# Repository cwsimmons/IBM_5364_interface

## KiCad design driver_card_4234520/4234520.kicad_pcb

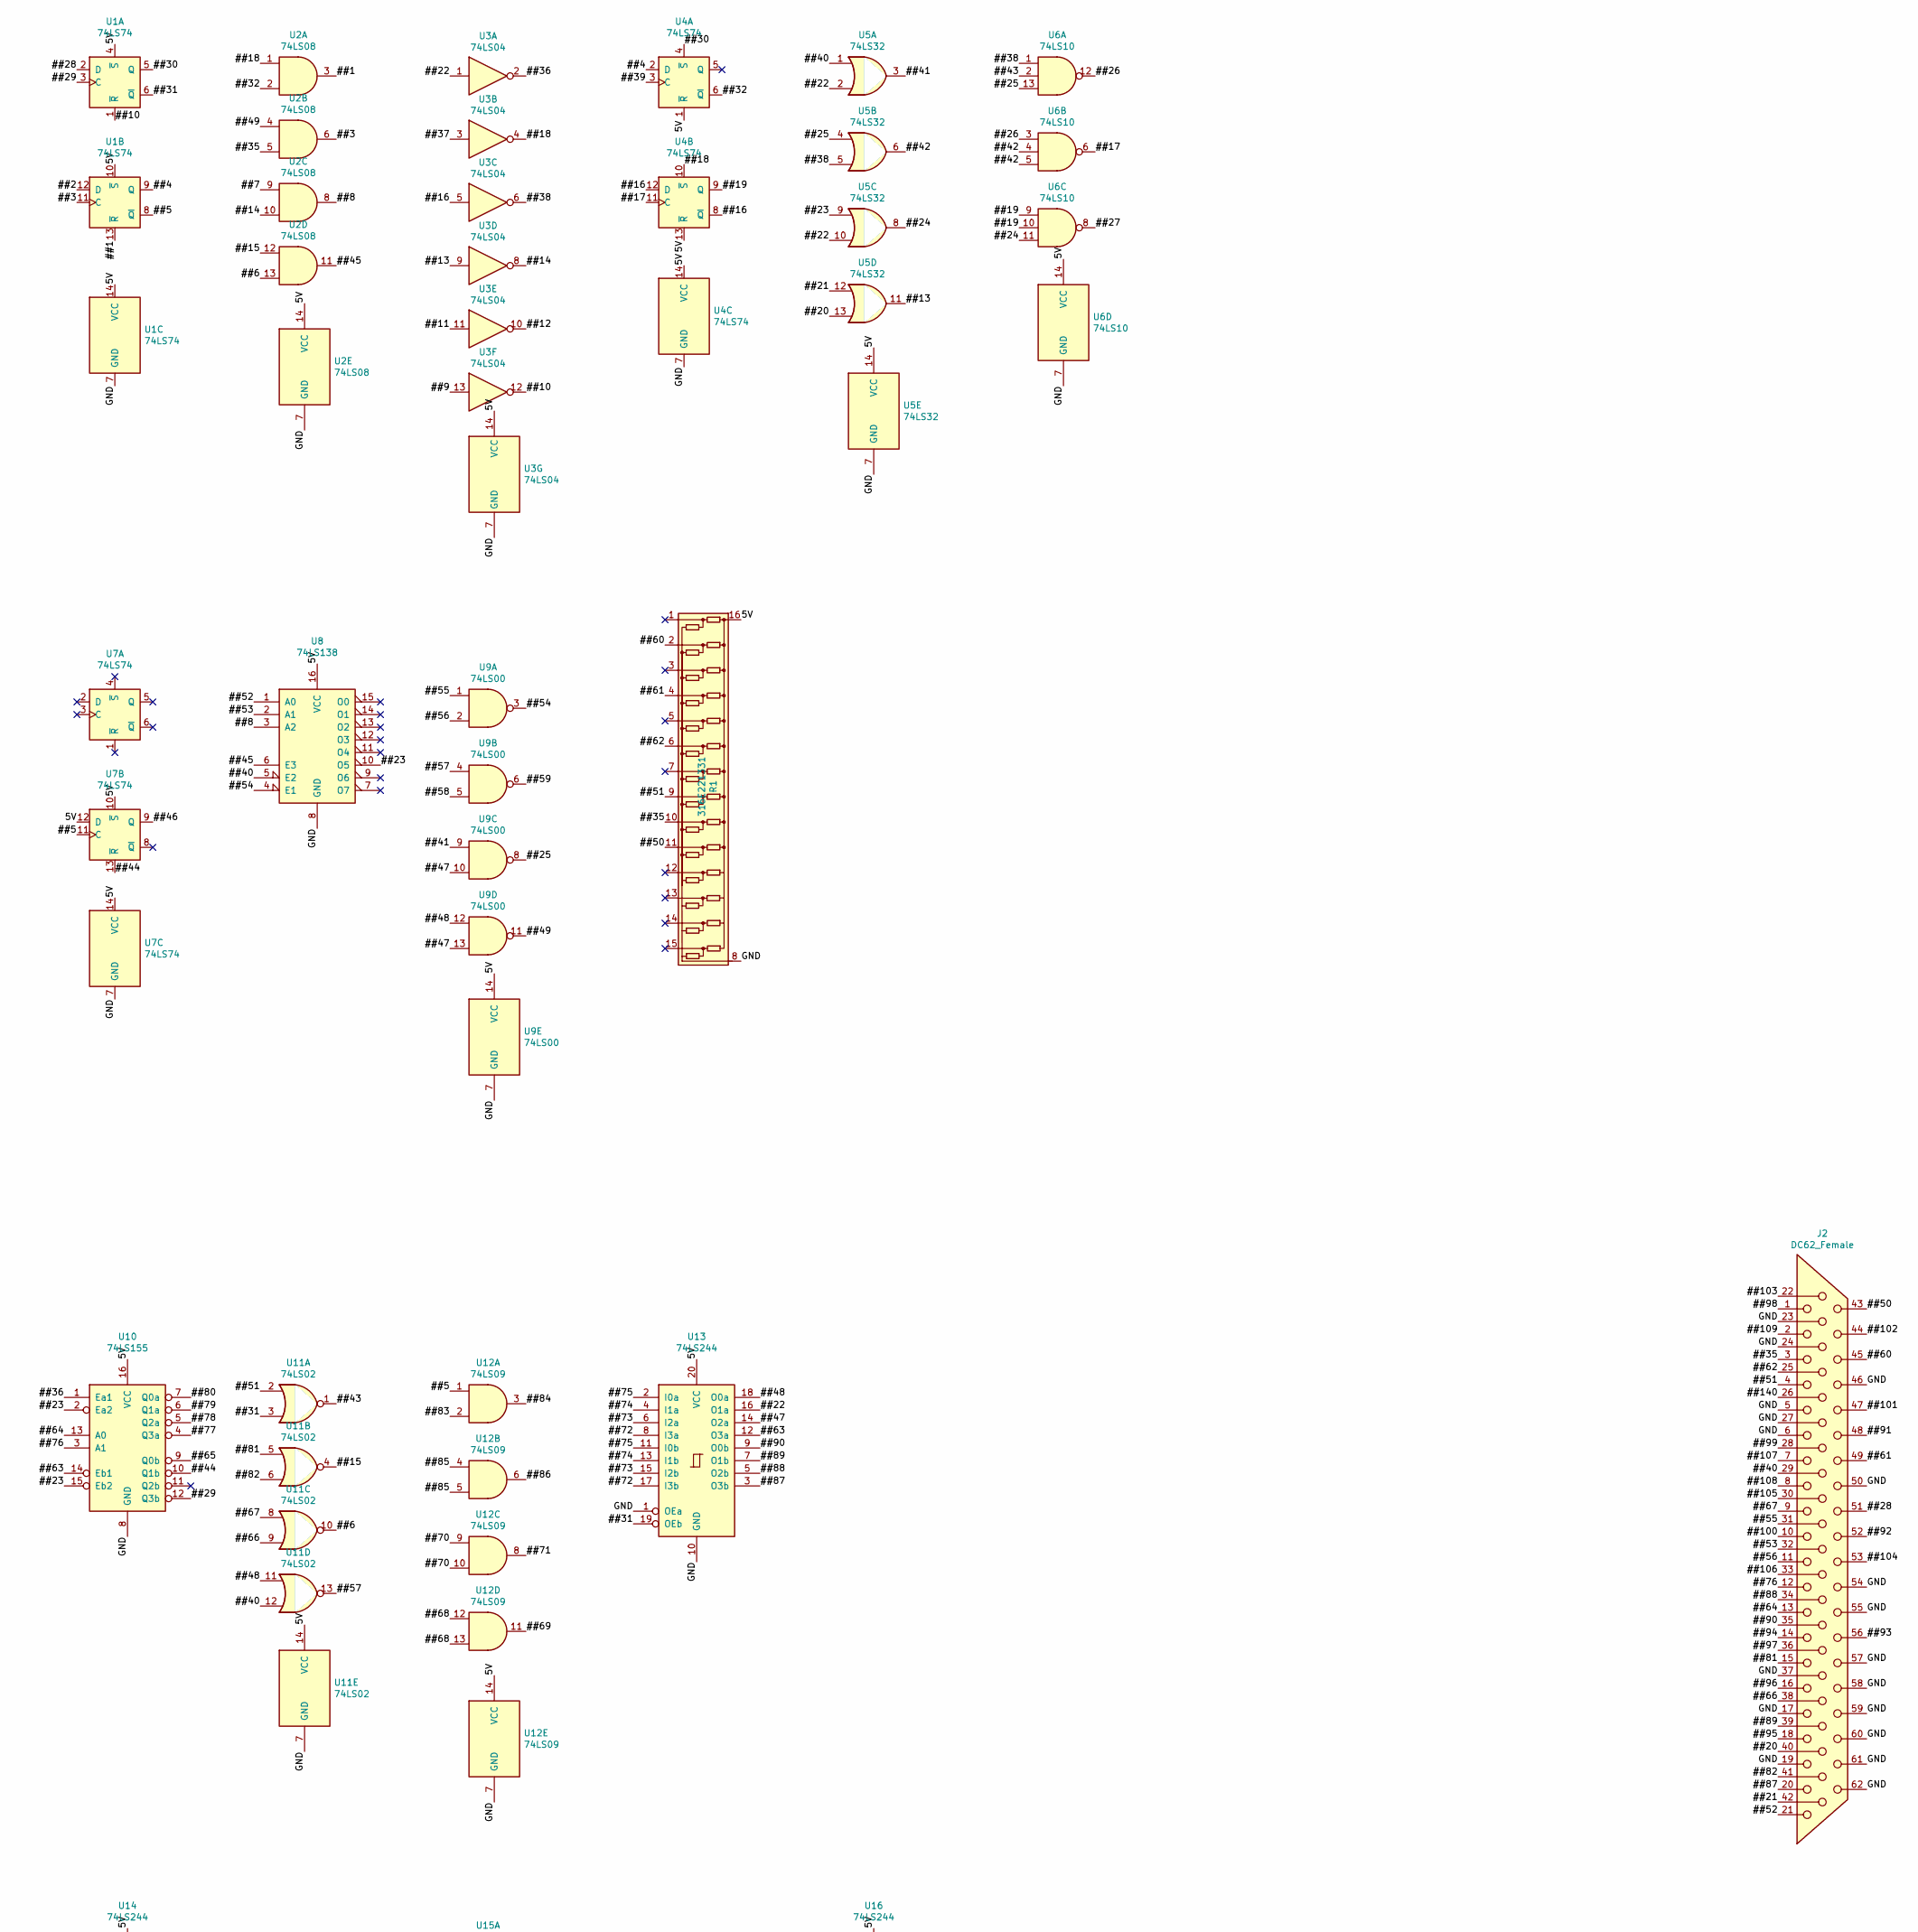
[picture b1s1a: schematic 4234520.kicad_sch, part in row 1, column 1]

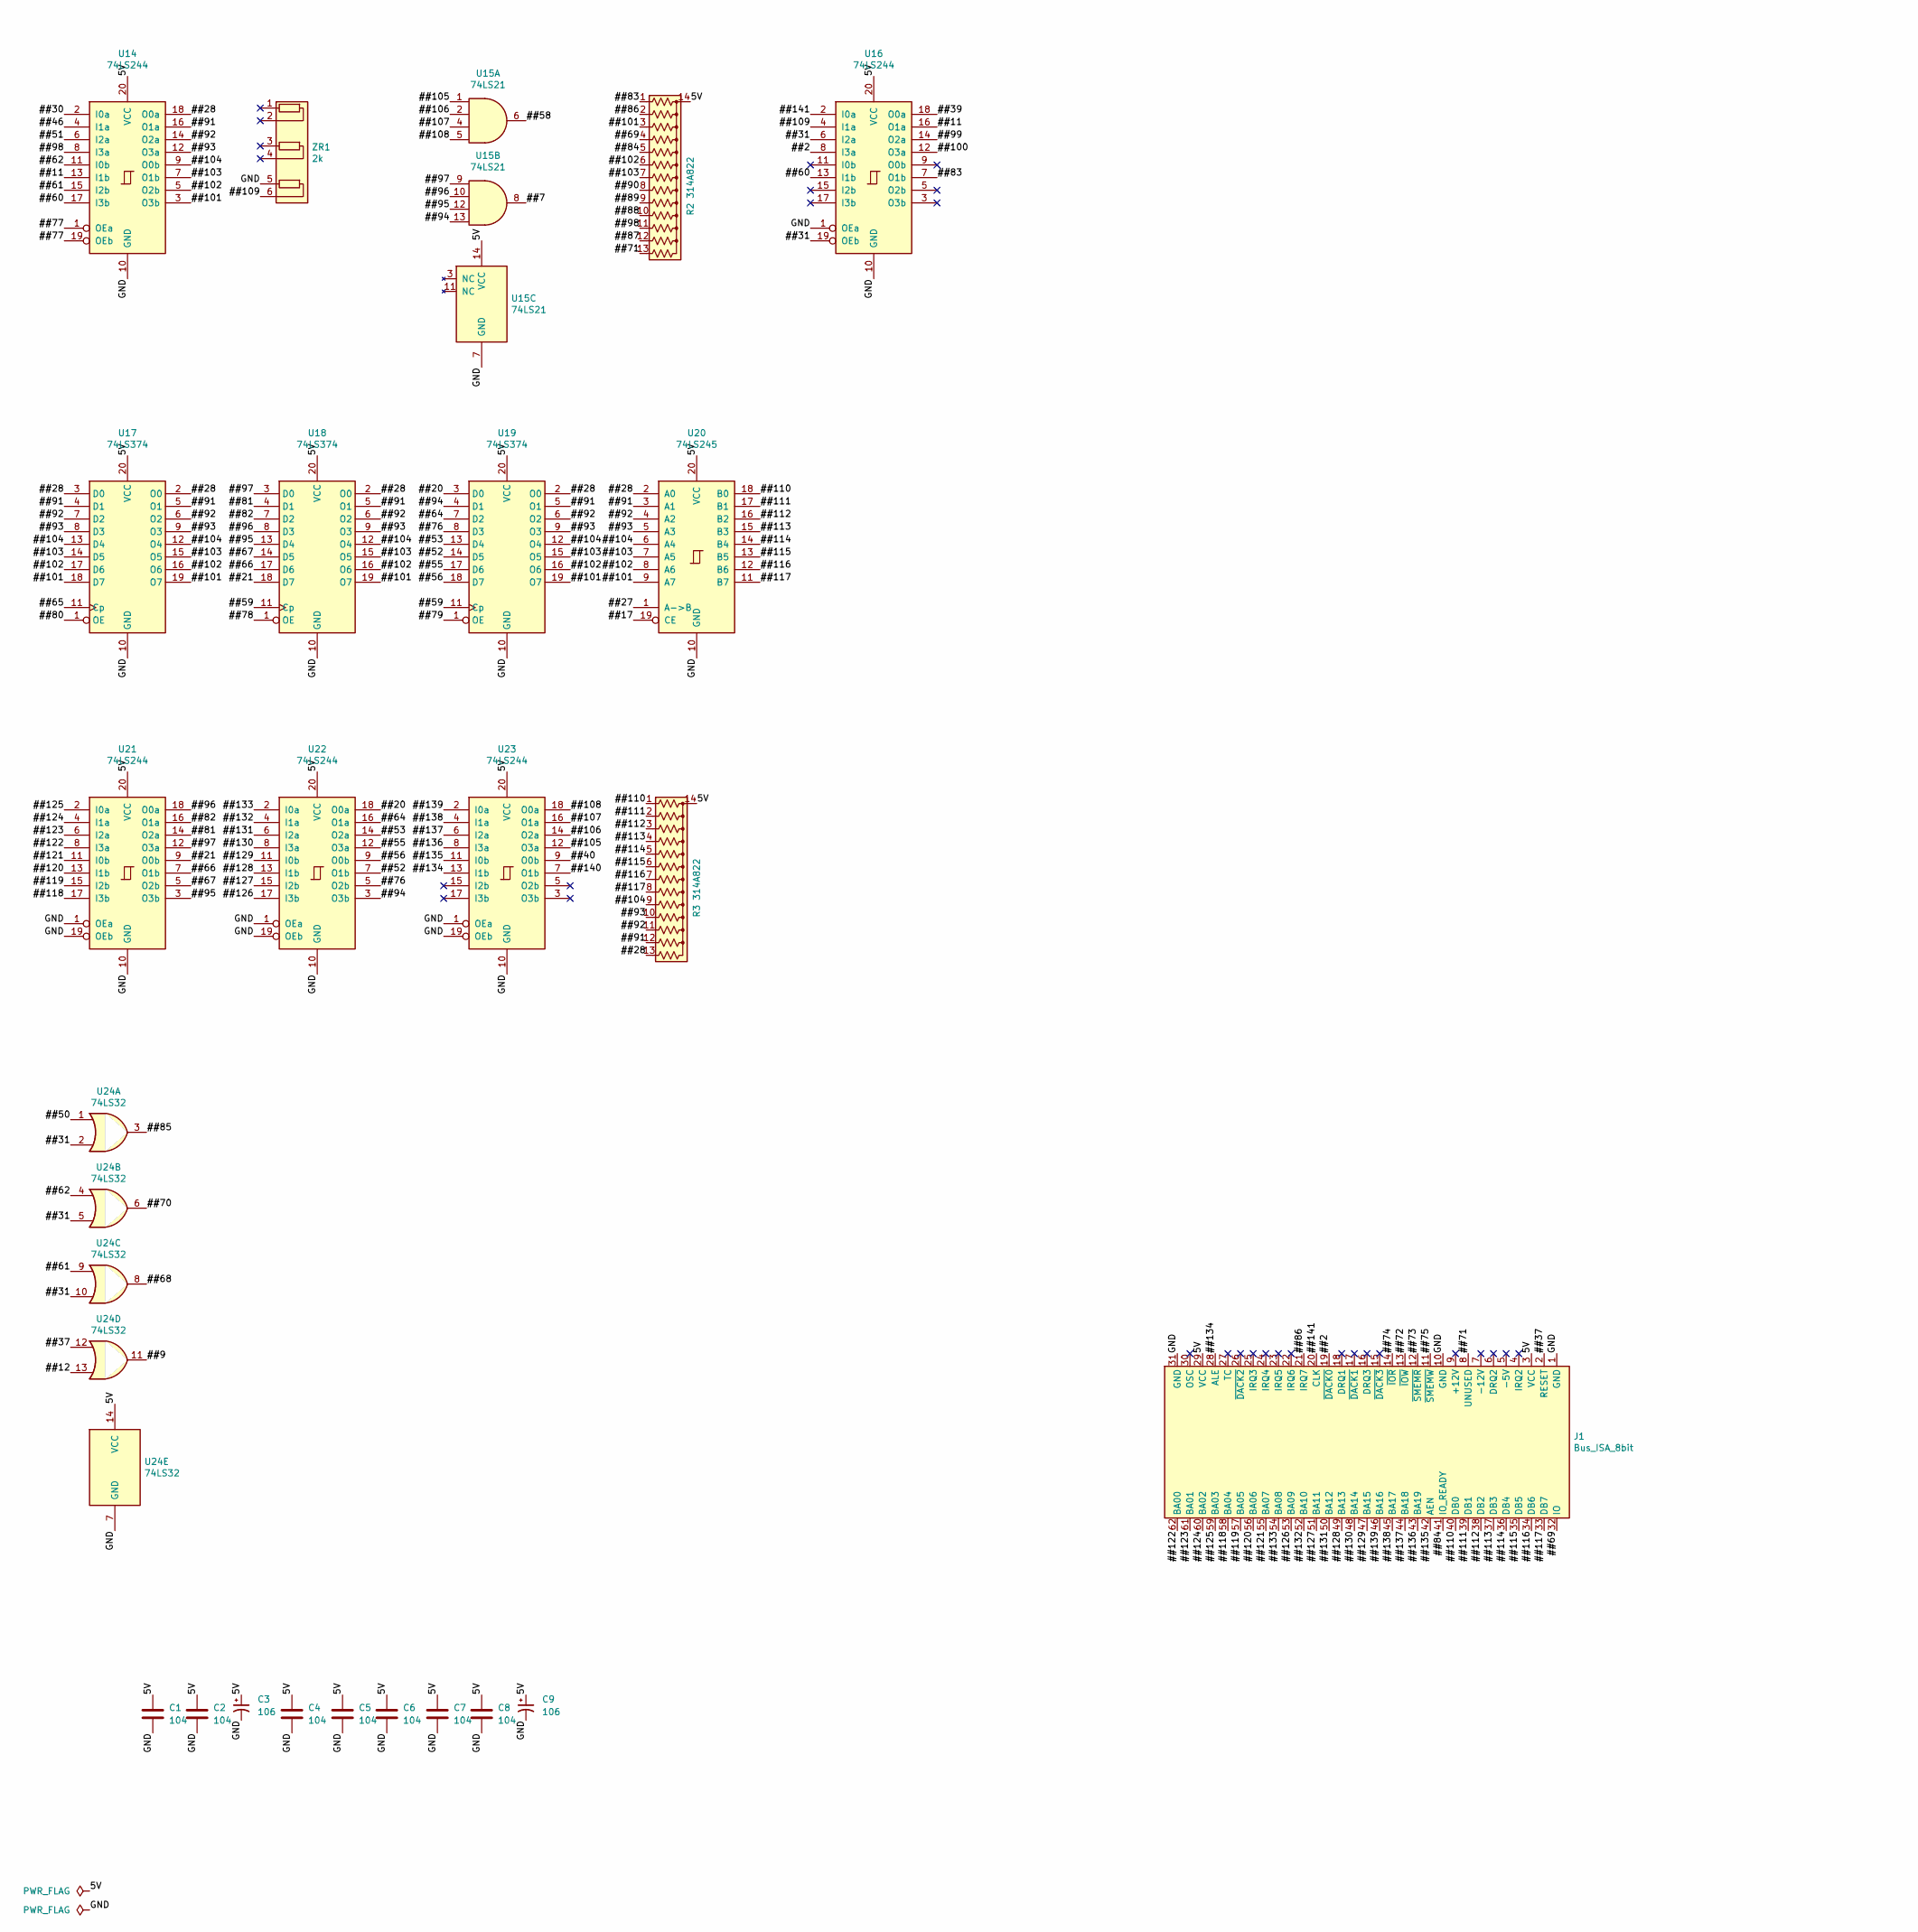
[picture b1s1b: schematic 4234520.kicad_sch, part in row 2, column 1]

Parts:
C1, C2, C4, C5, C6, C7, C8: 104; C_Rect_L7.0mm_W2.0mm_P5.00mm
C3, C9: 106; C_Rect_L7.0mm_W2.0mm_P5.00mm
J1: Bus_ISA_8bit; BUS_XT
J2: DC62_Female; DSUB-62-HD_Female_Horizontal_P2.41x1.98mm_EdgePinOffset3.03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
R1: 316E221331; DIP-16_W7.62mm
R2, R3: 314A822; DIP-14_W7.62mm
U1, U4, U7: 74LS74; DIP-14_W7.62mm
U2: 74LS08; DIP-14_W7.62mm
U3: 74LS04; DIP-14_W7.62mm
U5, U24: 74LS32; DIP-14_W7.62mm
U6: 74LS10; DIP-14_W7.62mm
U8: 74LS138; DIP-16_W7.62mm
U9: 74LS00; DIP-14_W7.62mm
U10: 74LS155; DIP-16_W7.62mm
U11: 74LS02; DIP-14_W7.62mm
U12: 74LS09; DIP-14_W7.62mm
U13, U14, U16, U21, U22, U23: 74LS244; DIP-20_W7.62mm
U15: 74LS21; DIP-14_W7.62mm
U17, U18, U19: 74LS374; DIP-20_W7.62mm
U20: 74LS245; DIP-20_W7.62mm
ZR1: 2k; R_Array_SIP6

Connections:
/5V: C1.1, C2.1, C3.1, C4.1, C5.1, C6.1, C7.1, C8.1, C9.1, J1.3 (VCC), J1.29 (VCC), R1.16 (COM1), R2.14 (common), R3.14 (common), U1.4 (~S), U1.10 (~S), U1.14 (VCC), U2.14 (VCC), U3.14 (VCC), U4.1 (~R), U4.13 (~R), U4.14 (VCC), U5.14 (VCC), U6.14 (VCC), U7.10 (~S), U7.12 (D), U7.14 (VCC), U8.16 (VCC), U9.14 (VCC), U10.16 (VCC), U11.14 (VCC), U12.14 (VCC), U13.20 (VCC), U14.20 (VCC), U15.14 (VCC), U16.20 (VCC), U17.20 (VCC), U18.20 (VCC), U19.20 (VCC), U20.20 (VCC), U21.20 (VCC), U22.20 (VCC), U23.20 (VCC), U24.14 (VCC)
/##1: U1.13 (~R), U2.3
/##2: J1.19 (~DACK0), U1.12 (D), U16.8 (I3a)
/##3: U1.11 (C), U2.6
/##4: U1.9 (Q), U4.2 (D)
/##5: U1.8 (~Q), U7.11 (C), U12.1
/##6: U2.13, U11.10
/##7: U2.9, U15.8
/##8: U2.8, U8.3 (A2)
/##9: U3.13, U24.11
/##10: U1.1 (~R), U3.12
/##11: U3.11, U14.13 (I1b), U16.16 (O1a)
/##12: U3.10, U24.13
/##13: U3.9, U5.11
/##14: U2.10, U3.8
/##15: U2.12, U11.4
/##16: U3.5, U4.8 (~Q), U4.12 (D)
/##17: U4.11 (C), U6.6, U20.19 (CE)
/##18: U2.1, U3.4, U4.10 (~S)
/##19: U4.9 (Q), U6.9, U6.10
/##20: J2.40, U5.13, U19.3 (D0), U22.18 (O0a)
/##21: J2.42, U5.12, U18.18 (D7), U21.9 (O0b)
/##22: U3.1, U5.2, U5.10, U13.16 (O1a)
/##23: U5.9, U8.10 (O5), U10.2 (Ea2), U10.15 (Eb2)
/##24: U5.8, U6.11
/##25: U5.4, U6.13, U9.8
/##26: U6.3, U6.12
/##27: U6.8, U20.1 (A->B)
/##28: J2.51, R3.13 (R13), U1.2 (D), U14.18 (O0a), U17.2 (O0), U17.3 (D0), U18.2 (O0), U19.2 (O0), U20.2 (A0)
/##29: U1.3 (C), U10.12 (Q3b)
/##30: U1.5 (Q), U4.4 (~S), U14.2 (I0a)
/##31: U1.6 (~Q), U11.3, U13.19 (OEb), U16.6 (I2a), U16.19 (OEb), U24.2, U24.5, U24.10
/##32: U2.2, U4.6 (~Q)
/##35: J2.3, R1.10 (R9), U2.5
/##36: U3.2, U10.1 (Ea1)
/##37: J1.2 (RESET), U3.3, U24.12
/##38: U3.6, U5.5, U6.1
/##39: U4.3 (C), U16.18 (O0a)
/##40: J2.29, U5.1, U8.5 (E2), U11.12, U23.9 (O0b)
/##41: U5.3, U9.9
/##42: U5.6, U6.4, U6.5
/##43: U6.2, U11.1
/##44: U7.13 (~R), U10.10 (Q1b)
/##45: U2.11, U8.6 (E3)
/##46: U7.9 (Q), U14.4 (I1a)
/##47: U9.10, U9.13, U13.14 (O2a)
/##48: U9.12, U11.11, U13.18 (O0a)
/##49: U2.4, U9.11
/##50: J2.43, R1.11 (R10), U24.1
/##51: J2.4, R1.9 (R8), U11.2, U14.6 (I2a)
/##52: J2.21, U8.1 (A0), U19.14 (D5), U22.7 (O1b)
/##53: J2.32, U8.2 (A1), U19.13 (D4), U22.14 (O2a)
/##54: U8.4 (E1), U9.3
/##55: J2.31, U9.1, U19.17 (D6), U22.12 (O3a)
/##56: J2.11, U9.2, U19.18 (D7), U22.9 (O0b)
/##57: U9.4, U11.13
/##58: U9.5, U15.6
/##59: U9.6, U18.11 (Cp), U19.11 (Cp)
/##60: J2.45, R1.2 (R2), U14.17 (I3b), U16.13 (I1b)
/##61: J2.49, R1.4 (R4), U14.15 (I2b), U24.9
/##62: J2.25, R1.6 (R6), U14.11 (I0b), U24.4
/##63: U10.14 (Eb1), U13.12 (O3a)
/##64: J2.13, U10.13 (A0), U19.7 (D2), U22.16 (O1a)
/##65: U10.9 (Q0b), U17.11 (Cp)
/##66: J2.38, U11.9, U18.17 (D6), U21.7 (O1b)
/##67: J2.9, U11.8, U18.14 (D5), U21.5 (O2b)
/##68: U12.12, U12.13, U24.8
/##69: J1.32 (IO), R2.4 (R4), U12.11
/##70: U12.9, U12.10, U24.6
/##71: J1.8 (UNUSED), R2.13 (R13), U12.8
/##72: J1.13 (~IOW), U13.8 (I3a), U13.17 (I3b)
/##73: J1.12 (~SMEMR), U13.6 (I2a), U13.15 (I2b)
/##74: J1.14 (~IOR), U13.4 (I1a), U13.13 (I1b)
/##75: J1.11 (~SMEMW), U13.2 (I0a), U13.11 (I0b)
/##76: J2.12, U10.3 (A1), U19.8 (D3), U22.5 (O2b)
/##77: U10.4 (Q3a), U14.1 (OEa), U14.19 (OEb)
/##78: U10.5 (Q2a), U18.1 (OE)
/##79: U10.6 (Q1a), U19.1 (OE)
/##80: U10.7 (Q0a), U17.1 (OE)
/##81: J2.15, U11.5, U18.4 (D1), U21.14 (O2a)
/##82: J2.41, U11.6, U18.7 (D2), U21.16 (O1a)
/##83: R2.1 (R1), U12.2, U16.7 (O1b)
/##84: J1.41 (IO_READY), R2.5 (R5), U12.3
/##85: U12.4, U12.5, U24.3
/##86: J1.21 (IRQ7), R2.2 (R2), U12.6
/##87: J2.20, R2.12 (R12), U13.3 (O3b)
/##88: J2.34, R2.10 (R10), U13.5 (O2b)
/##89: J2.39, R2.9 (R9), U13.7 (O1b)
/##90: J2.35, R2.8 (R8), U13.9 (O0b)
/##91: J2.48, R3.12 (R12), U14.16 (O1a), U17.4 (D1), U17.5 (O1), U18.5 (O1), U19.5 (O1), U20.3 (A1)
/##92: J2.52, R3.11 (R11), U14.14 (O2a), U17.6 (O2), U17.7 (D2), U18.6 (O2), U19.6 (O2), U20.4 (A2)
/##93: J2.56, R3.10 (R10), U14.12 (O3a), U17.8 (D3), U17.9 (O3), U18.9 (O3), U19.9 (O3), U20.5 (A3)
/##94: J2.14, U15.13, U19.4 (D1), U22.3 (O3b)
/##95: J2.18, U15.12, U18.13 (D4), U21.3 (O3b)
/##96: J2.16, U15.10, U18.8 (D3), U21.18 (O0a)
/##97: J2.36, U15.9, U18.3 (D0), U21.12 (O3a)
/##98: J2.1, R2.11 (R11), U14.8 (I3a)
/##99: J2.28, U16.14 (O2a)
/##100: J2.10, U16.12 (O3a)
/##101: J2.47, R2.3 (R3), U14.3 (O3b), U17.18 (D7), U17.19 (O7), U18.19 (O7), U19.19 (O7), U20.9 (A7)
/##102: J2.44, R2.6 (R6), U14.5 (O2b), U17.16 (O6), U17.17 (D6), U18.16 (O6), U19.16 (O6), U20.8 (A6)
/##103: J2.22, R2.7 (R7), U14.7 (O1b), U17.14 (D5), U17.15 (O5), U18.15 (O5), U19.15 (O5), U20.7 (A5)
/##104: J2.53, R3.9 (R9), U14.9 (O0b), U17.12 (O4), U17.13 (D4), U18.12 (O4), U19.12 (O4), U20.6 (A4)
/##105: J2.30, U15.1, U23.12 (O3a)
/##106: J2.33, U15.2, U23.14 (O2a)
/##107: J2.7, U15.4, U23.16 (O1a)
/##108: J2.8, U15.5, U23.18 (O0a)
/##109: J2.2, U16.4 (I1a), ZR1.6 (R3.2)
/##110: J1.40 (DB0), R3.1 (R1), U20.18 (B0)
/##111: J1.39 (DB1), R3.2 (R2), U20.17 (B1)
/##112: J1.38 (DB2), R3.3 (R3), U20.16 (B2)
/##113: J1.37 (DB3), R3.4 (R4), U20.15 (B3)
/##114: J1.36 (DB4), R3.5 (R5), U20.14 (B4)
/##115: J1.35 (DB5), R3.6 (R6), U20.13 (B5)
/##116: J1.34 (DB6), R3.7 (R7), U20.12 (B6)
/##117: J1.33 (DB7), R3.8 (R8), U20.11 (B7)
/##118: J1.58 (BA04), U21.17 (I3b)
/##119: J1.57 (BA05), U21.15 (I2b)
/##120: J1.56 (BA06), U21.13 (I1b)
/##121: J1.55 (BA07), U21.11 (I0b)
/##122: J1.62 (BA00), U21.8 (I3a)
/##123: J1.61 (BA01), U21.6 (I2a)
/##124: J1.60 (BA02), U21.4 (I1a)
/##125: J1.59 (BA03), U21.2 (I0a)
/##126: J1.53 (BA09), U22.17 (I3b)
/##127: J1.51 (BA11), U22.15 (I2b)
/##128: J1.49 (BA13), U22.13 (I1b)
/##129: J1.47 (BA15), U22.11 (I0b)
/##130: J1.48 (BA14), U22.8 (I3a)
/##131: J1.50 (BA12), U22.6 (I2a)
/##132: J1.52 (BA10), U22.4 (I1a)
/##133: J1.54 (BA08), U22.2 (I0a)
/##134: J1.28 (ALE), U23.13 (I1b)
/##135: J1.42 (AEN), U23.11 (I0b)
/##136: J1.43 (BA19), U23.8 (I3a)
/##137: J1.44 (BA18), U23.6 (I2a)
/##138: J1.45 (BA17), U23.4 (I1a)
/##139: J1.46 (BA16), U23.2 (I0a)
/##140: J2.26, U23.7 (O1b)
/##141: J1.20 (CLK), U16.2 (I0a)
/GND: C1.2, C2.2, C3.2, C4.2, C5.2, C6.2, C7.2, C8.2, C9.2, J1.1 (GND), J1.10 (GND), J1.31 (GND), J2.5, J2.6, J2.17, J2.19, J2.23, J2.24, J2.27, J2.37, J2.46, J2.50, J2.54, J2.55, J2.57, J2.58, J2.59, J2.60, J2.61, J2.62, R1.8 (COM2), U1.7 (GND), U2.7 (GND), U3.7 (GND), U4.7 (GND), U5.7 (GND), U6.7 (GND), U7.7 (GND), U8.8 (GND), U9.7 (GND), U10.8 (GND), U11.7 (GND), U12.7 (GND), U13.1 (OEa), U13.10 (GND), U14.10 (GND), U15.7 (GND), U16.1 (OEa), U16.10 (GND), U17.10 (GND), U18.10 (GND), U19.10 (GND), U20.10 (GND), U21.1 (OEa), U21.10 (GND), U21.19 (OEb), U22.1 (OEa), U22.10 (GND), U22.19 (OEb), U23.1 (OEa), U23.10 (GND), U23.19 (OEb), U24.7 (GND), ZR1.5 (R3.1)

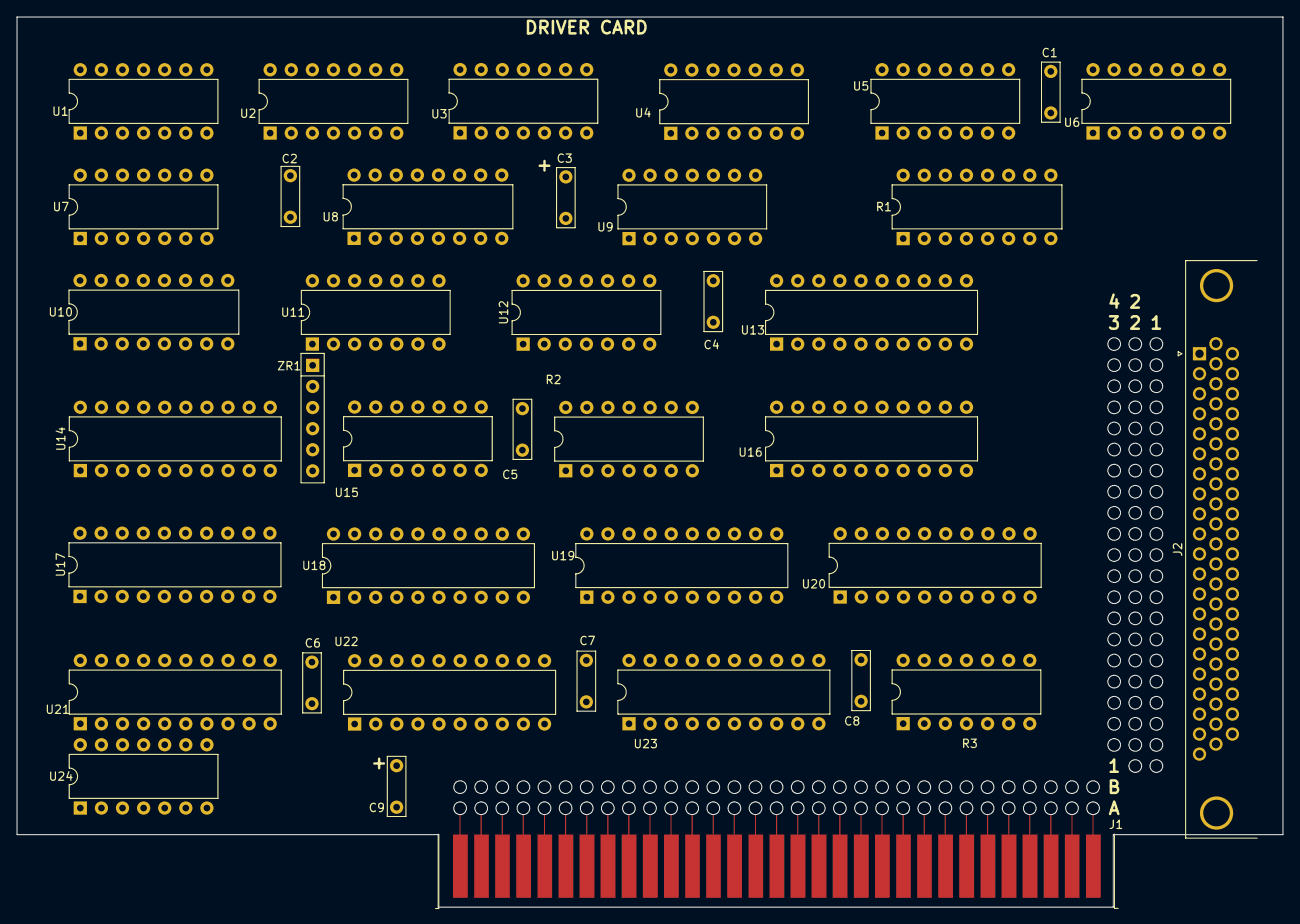
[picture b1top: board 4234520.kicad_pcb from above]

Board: 4 copper layers, 152.4 x 107.2 mm, 39 parts (0 on the bottom side), 141 nets.

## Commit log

2022-08-27 Place parts
2024-01-21 Do some tracing
2024-01-24 Tracing finished
2024-01-24 Add PDF
2024-01-24 copy over PCB layout from earlier project add custom symbols for r networks add custom footprint for ISA XT bus add and label test point vias add filter caps missing from original schematic
2024-01-25 make library paths relative convert to 4 layer pcb add gnd and 5v planes symbol cleanup ERC zero errors!
2024-01-25 add PCB images and attempt to align them
2024-01-25 Add redrawn schematic, courtesy of Tube Time (@schlae)
2024-01-25 update tubetime's sch for r-pack symbols, clean up DRC
2024-01-25 add back filter caps
2024-01-25 replace cap footprints, update nets, run ISA bus and DC62 traces to test points
2024-01-26 remove giant bitmaps, will replace with less giant bitmaps later
2024-01-26 import tubetime's PCB layout, reapply symbol changes and caps, clean up some ERC
